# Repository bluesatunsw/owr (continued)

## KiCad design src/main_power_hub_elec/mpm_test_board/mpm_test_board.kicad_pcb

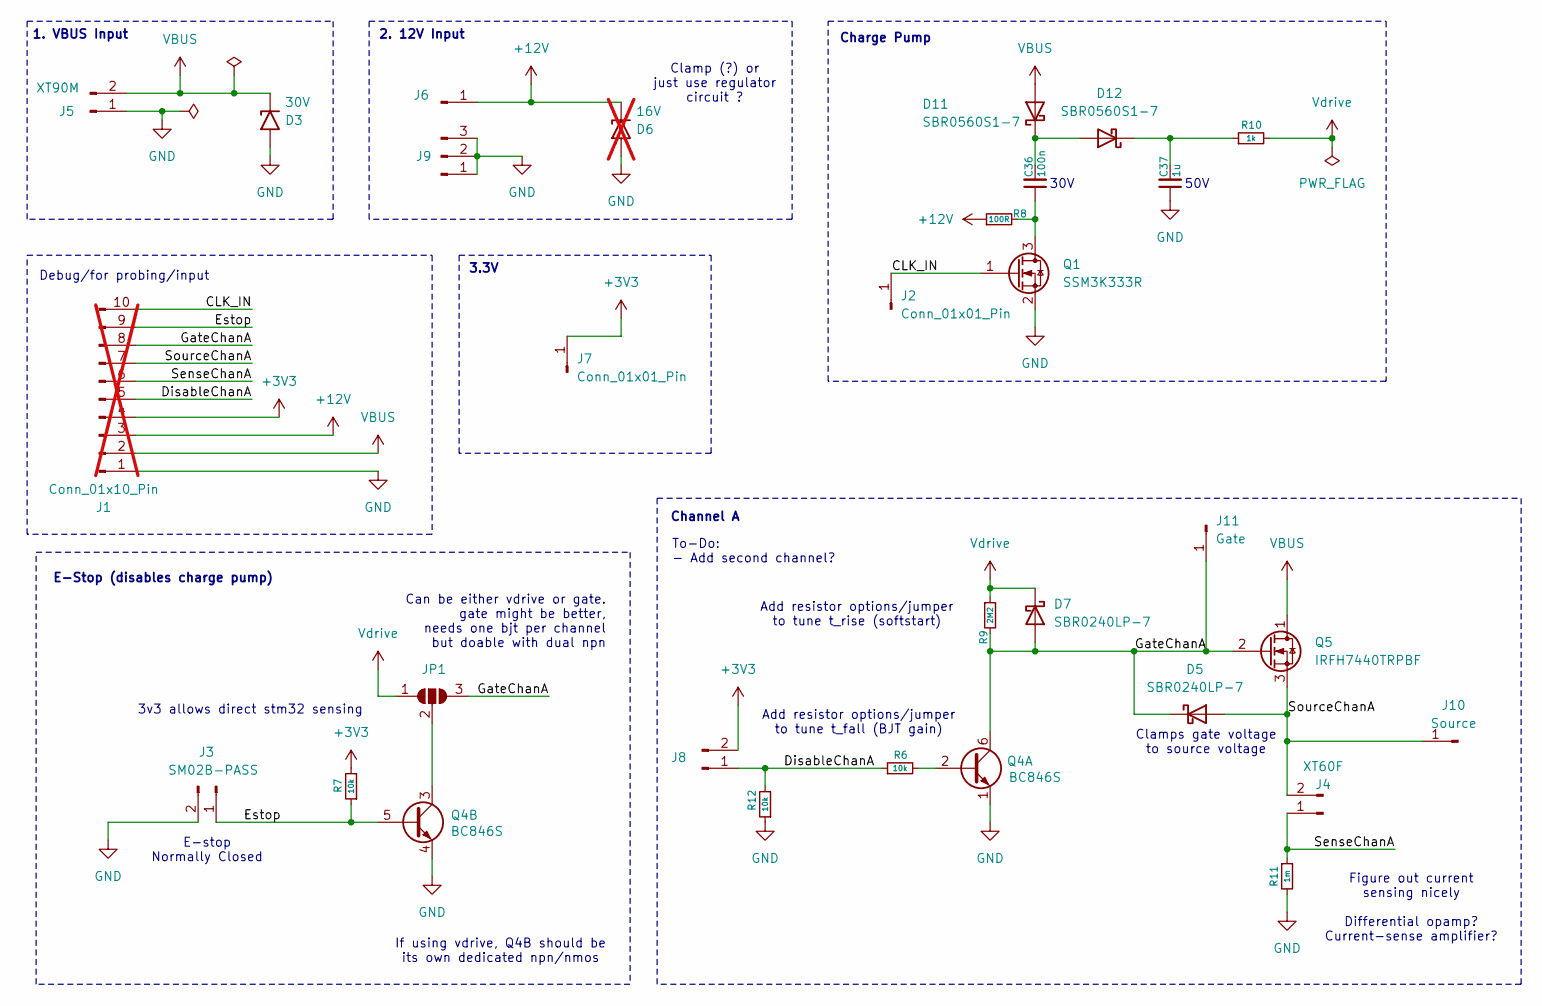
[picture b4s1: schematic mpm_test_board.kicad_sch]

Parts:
C36: 100n; C_0603_1608Metric
C37: 1u; C_1206_3216Metric
D3: 30V; D_SMF
D5, D7: SBR0240LP-7; D_SOD-882D
D6: 16V; not fitted
D11, D12: SBR0560S1-7; D_SOD-123
J1: Conn_01x10_Pin; PinHeader_1x10_P2.54mm_Vertical; not fitted
J2, J7: Conn_01x01_Pin; PinHeader_1x01_P2.54mm_Vertical
J3: SM02B-PASS
J4: XT60F; AMASS_XT60PW-F_1x02_P7.20mm_Horizontal
J5: XT90M; AMASS_XT90PW-M_1x02_P10.90mm_Horizontal
J6: PinHeader_1x01_P2.54mm_Vertical
J8: PinHeader_1x02_P2.54mm_Vertical
J9: Conn_01x10_Pin; PinHeader_1x03_P2.54mm_Vertical
J10: Source; PinHeader_1x01_P2.54mm_Vertical
J11: Gate; PinHeader_1x01_P2.54mm_Vertical
JP1: SolderJumper_3_Open; SolderJumper-3_P1.3mm_Open_Pad1.0x1.5mm_NumberLabels
Q1: SSM3K333R; SOT-23-3
Q4: BC846S; SOT-363
Q5: IRFH7440TRPBF; PQFN_5x6mm_E_DGS
R6, R7, R12: 10k; R_0402_1005Metric
R8: 100R; R_0402_1005Metric
R9: 2M2; R_0402_1005Metric
R10: 1k; R_0402_1005Metric
R11: 1m; R_2512_6332Metric

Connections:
+3V3: J1.4, J7.1 (Pin_1_1), J8.2, R7.2
+12V: D6.1 (A1), J1.3, J6.1 (Pin_1_1), R8.1
/CLK_IN: J1.10, J2.1 (Pin_1_1), Q1.1 (G)
/DisableChanA: J1.5, J8.1, R6.1, R12.2
/Estop: J1.9, J3.1, Q4.5 (B2), R7.1
/GateChanA: D5.1 (K), D7.2 (A), J1.8, J11.1 (Pin_1_1), JP1.3 (B), Q4.6 (C1), Q5.2 (G), R9.2
/SenseChanA: J1.6, J4.1, R11.1
/SourceChanA: D5.2 (A), J1.7, J4.2, J10.1 (Pin_1_1), Q5.3 (S)
GND: C37.1, D3.2 (A2), D6.2 (A2), J1.1, J3.2, J5.1, J9.1, J9.2, J9.3, Q1.2 (S), Q4.1 (E1), Q4.4 (E2), R11.2, R12.1
unnamed: C36.2, D11.1 (K), D12.2 (A)
unnamed: C37.2, D12.1 (K), R10.1
unnamed: JP1.2 (C), Q4.3 (C2)
unnamed: C36.1, Q1.3 (D), R8.2
unnamed: Q4.2 (B1), R6.2
VBUS: D3.1 (A1), D11.2 (A), J1.2, J5.2, Q5.1 (D)
Vdrive: D7.1 (K), JP1.1 (A), R9.1, R10.2

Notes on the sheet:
E-Stop (disables charge pump)
E-stop Normally Closed
3.3V
Figure out current sensing nicely Differential opamp? Current-sense amplifier?
Clamp (?) or just use regulator circuit ?
2. 12V Input
Charge Pump
50V
3v3 allows direct stm32 sensing
Debug/for probing/input
Can be either vdrive or gate. gate might be better, needs one bjt per channel but doable with dual npn
Add resistor options/jumper to tune t_fall (BJT gain)
30V
Channel A
1. VBUS Input
If using vdrive, Q4B should be its own dedicated npn/nmos
Clamps gate voltage to source voltage
Add resistor options/jumper to tune t_rise (softstart)
To-Do: - Add second channel?

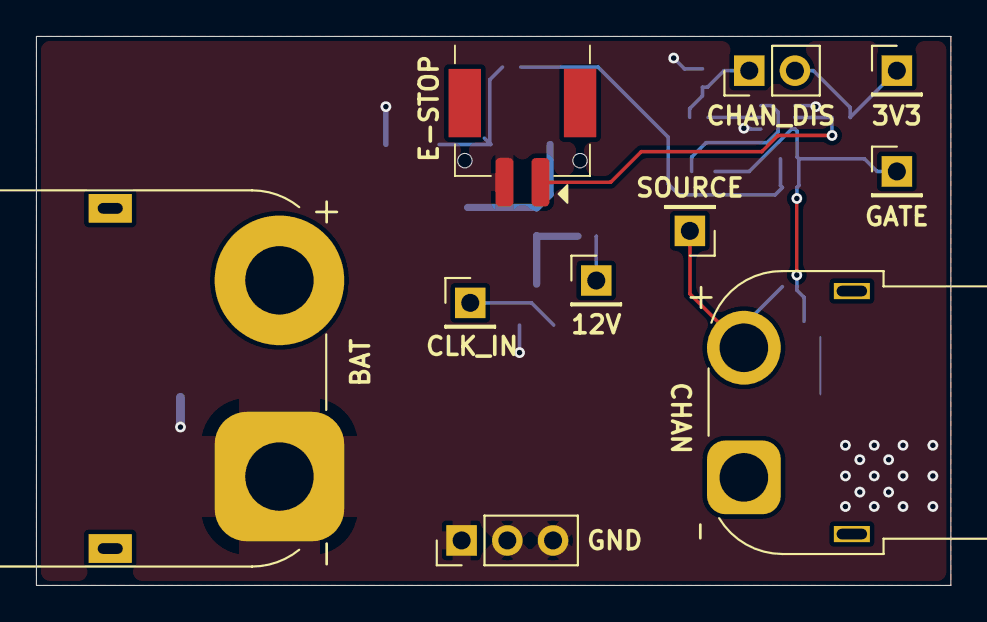
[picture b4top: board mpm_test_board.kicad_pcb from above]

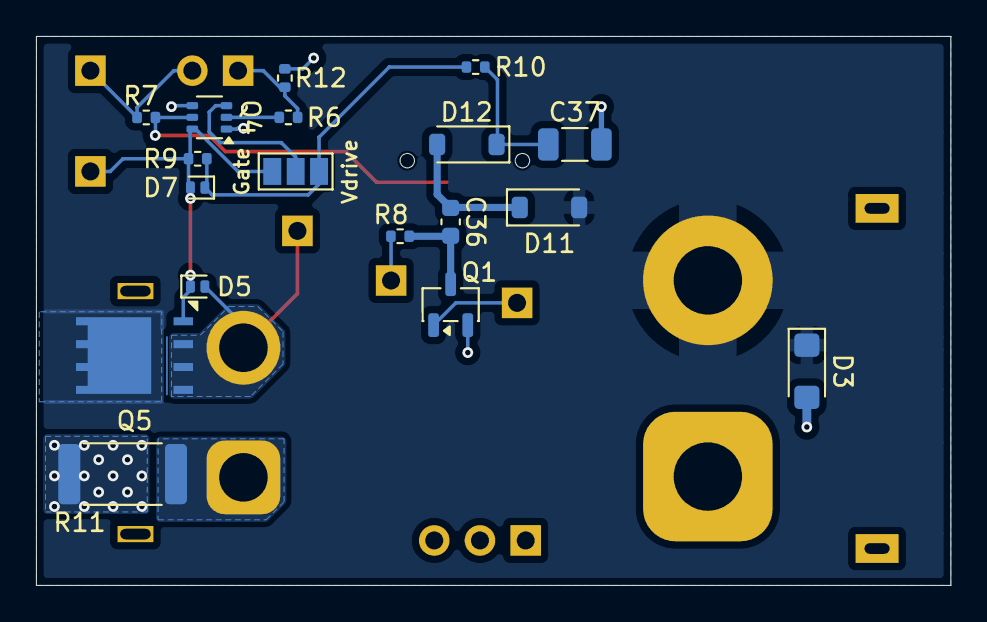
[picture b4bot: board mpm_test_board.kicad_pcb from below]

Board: 2 copper layers, 50.8 x 30.5 mm, 28 parts (18 on the bottom side), 16 nets.

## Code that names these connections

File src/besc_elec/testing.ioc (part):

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Mcu.Name=STM32G474R(B-C-E)Tx
Mcu.Package=LQFP64
Mcu.UserName=STM32G474RBTx
PA0.GPIOParameters=GPIO_Label
PA0.GPIO_Label=HALL_W
PA0.Signal=S_TIM5_CH1
PA1.GPIOParameters=GPIO_Label
PA1.GPIO_Label=HALL_V
PA1.Signal=S_TIM5_CH2
PA11.Mode=FDCAN_Activate
PA11.Signal=FDCAN1_RX
PA12.Mode=FDCAN_Activate
PA12.Signal=FDCAN1_TX
PA13.Mode=Trace_Asynchronous_SW
PA13.Signal=SYS_JTMS-SWDIO
PA14.Mode=Trace_Asynchronous_SW
PA14.Signal=SYS_JTCK-SWCLK
PA15.Mode=I2C
PA15.Signal=I2C1_SCL
PA2.GPIOParameters=GPIO_Label
PA2.GPIO_Label=HALL_U
PA2.Signal=S_TIM5_CH3
PA3.GPIOParameters=GPIO_Label
PA3.GPIO_Label=SENS_A
PA3.Mode=IN4-Single-Ended
PA3.Signal=ADC1_IN4
PA4.GPIOParameters=GPIO_Label
PA4.GPIO_Label=DRV_CAL
PA4.Signal=GPIO_Output
PA5.GPIOParameters=GPIO_Label
PA5.GPIO_Label=PHS_B
PA5.Mode=IN13-Single-Ended
PA5.Signal=ADC2_IN13
PA6.GPIOParameters=GPIO_Label
PA6.GPIO_Label=SENS_B
PA6.Mode=IN3-Single-Ended
PA6.Signal=ADC2_IN3
PA7.Mode=IN4-Single-Ended
PA7.Signal=ADC2_IN4
PA8.GPIOParameters=GPIO_Label
PA8.GPIO_Label=VSENS
PA8.Mode=IN1-Differential
PA8.Signal=ADC5_IN1
PA9.GPIOParameters=GPIO_Label
PA9.GPIO_Label=TEMP_BRD
PA9.Mode=IN1-Differential
PA9.Signal=ADC5_IN2
PB0.GPIOParameters=GPIO_Label
PB0.GPIO_Label=PHS_C
PB0.Mode=IN12-Single-Ended
PB0.Signal=ADC3_IN12
PB1.GPIOParameters=GPIO_Label
PB1.GPIO_Label=SENS_C
PB1.Mode=IN1-Single-Ended
PB1.Signal=ADC3_IN1
PB10.GPIOParameters=GPIO_Label
PB10.GPIO_Label=DRV_FLT
PB10.Mode=Fault_Enable3
PB10.Signal=HRTIM1_FLT3
PB11.Mode=IN14-Single-Ended
PB11.Signal=ADC1_IN14
PB12.GPIOParameters=GPIO_Label
PB12.GPIO_Label=PWM_H3
PB12.Mode=Output_TC1TC2
PB12.Signal=HRTIM1_CHC1
PB13.GPIOParameters=GPIO_Label
PB13.GPIO_Label=PWM_L3
PB13.Mode=Output_TC1TC2
PB13.Signal=HRTIM1_CHC2
PB14.GPIOParameters=GPIO_Label
PB14.GPIO_Label=TEMP_MOT
PB14.Mode=IN4-Single-Ended
PB14.Signal=ADC4_IN4
PB3.Mode=Trace_Asynchronous_SW
PB3.Signal=SYS_JTDO-SWO
PB5.GPIOParameters=GPIO_Label
PB5.GPIO_Label=DRV_EN
PB5.Signal=GPIO_Output
PB6.GPIOParameters=GPIO_Label
PB6.GPIO_Label=SPI_CS
PB6.Signal=GPIO_Output
PB9.Mode=I2C
PB9.Signal=I2C1_SDA
PC0.GPIOParameters=GPIO_Label
PC0.GPIO_Label=PHS_A
PC0.Mode=IN6-Single-Ended
PC0.Signal=ADC1_IN6
PC1.Mode=IN7-Single-Ended
PC1.Signal=ADC2_IN7
PC10.Mode=Full_Duplex_Master
PC10.Signal=SPI3_SCK
PC11.Mode=Full_Duplex_Master
PC11.Signal=SPI3_MISO
PC12.Mode=Full_Duplex_Master
PC12.Signal=SPI3_MOSI
PC2.Mode=IN8-Single-Ended
PC2.Signal=ADC1_IN8
PC3.Mode=IN9-Single-Ended
PC3.Signal=ADC2_IN9
PC4.GPIOParameters=GPIO_Label
PC4.GPIO_Label=ARGB
PC4.Signal=GPIO_Output
PC6.GPIOParameters=GPIO_Label
PC6.GPIO_Label=PWM_H2
PC6.Mode=Output_TF1TF2
PC6.Signal=HRTIM1_CHF1
PC7.GPIOParameters=GPIO_Label
PC7.GPIO_Label=PWM_L2
PC7.Mode=Output_TF1TF2
PC7.Signal=HRTIM1_CHF2
PC8.GPIOParameters=GPIO_Label
PC8.GPIO_Label=PWM_H1
PC8.Mode=Output_TE1TE2
PC8.Signal=HRTIM1_CHE1
PC9.GPIOParameters=GPIO_Label
PC9.GPIO_Label=PWM_L1
PC9.Mode=Output_TE1TE2
PC9.Signal=HRTIM1_CHE2
PF0-OSC_IN.Mode=HSE-External-Oscillator
PF0-OSC_IN.Signal=RCC_OSC_IN
PF1-OSC_OUT.Mode=HSE-External-Oscillator
PF1-OSC_OUT.Signal=RCC_OSC_OUT
RCC.HSE_VALUE=8000000
RCC.SYSCLKFreq_VALUE=16000000
board=custom

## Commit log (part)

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2026-06-06 start spm firmware folder and init project
2026-06-20 Remove fun :(
2026-06-20 started on bringup code
2026-06-20 Firmware`1
2026-06-24 code + mx file fix
